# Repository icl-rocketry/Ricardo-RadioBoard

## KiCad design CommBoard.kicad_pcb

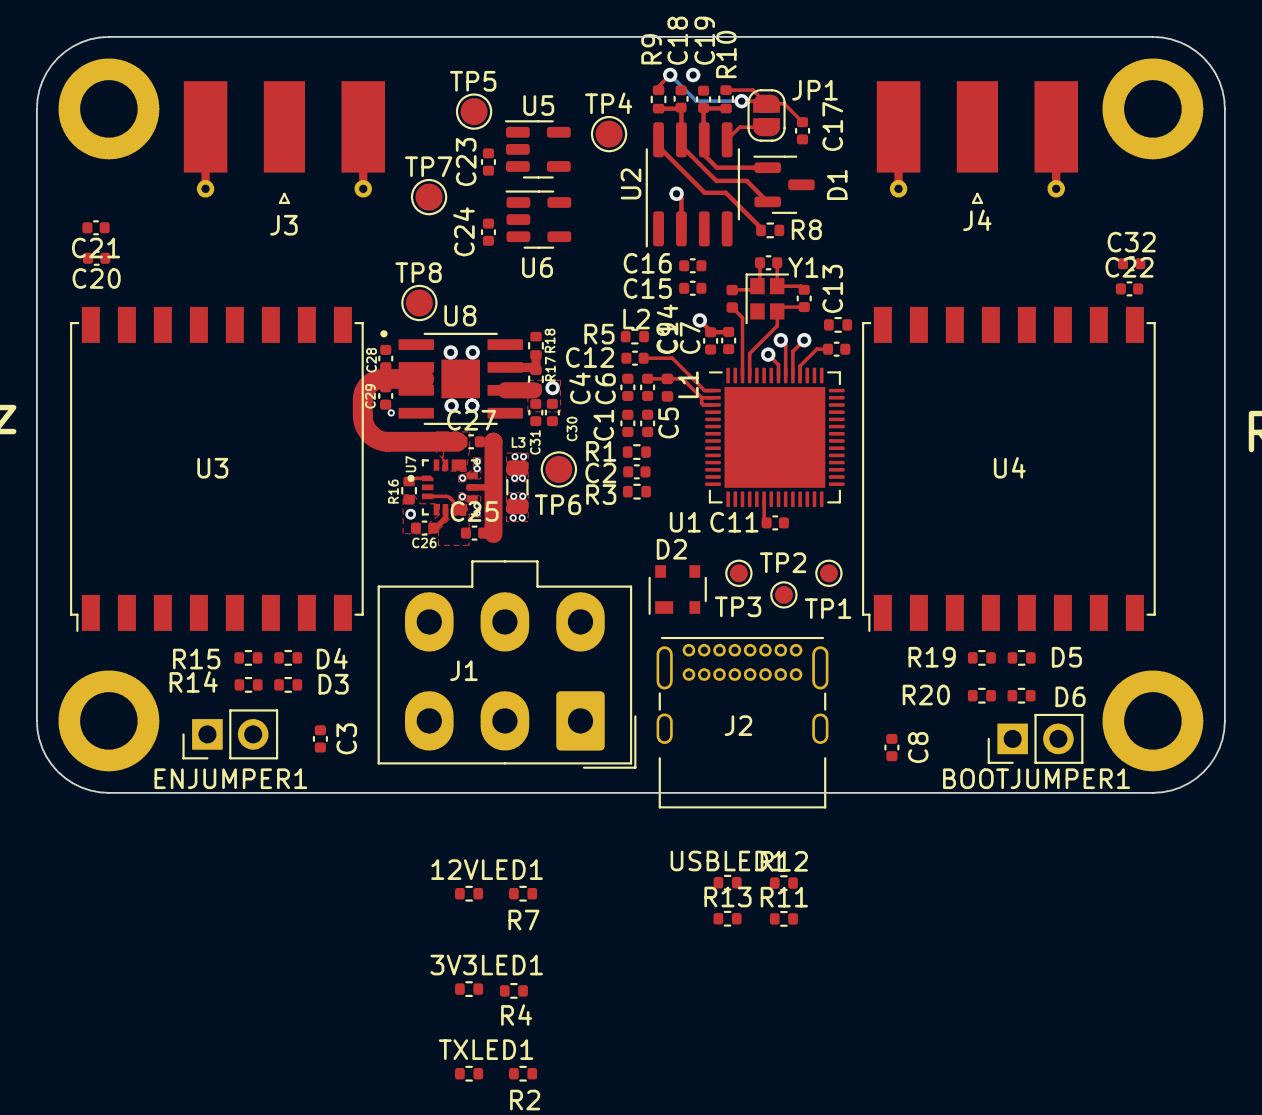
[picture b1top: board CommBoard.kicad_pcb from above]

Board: 4 copper layers, 66.0 x 42.0 mm, 93 parts (0 on the bottom side), 56 nets.

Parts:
3V3LED1: 3V3LED; R_0402_1005Metric
12VLED1: 12V_LED; R_0402_1005Metric
BOOTJUMPER1: Conn_01x02_Male; PinHeader_1x02_P2.54mm_Vertical
C1, C16, C20, C22, C25, C28, C30: 10uF; C_0402_1005Metric
C2, C4, C7, C26: 1uF; C_0402_1005Metric
C3, C5, C6, C8, C10, C11, C17, C21, C31, C32: 0.1uF; C_0402_1005Metric
C9: 10nF; C_0402_1005Metric
C12: 4.2pF; C_0402_1005Metric
C13, C14: C; C_0402_1005Metric
C15: 100nF; C_0402_1005Metric
C18, C19: 220pF; C_0402_1005Metric
C23, C24, C29: 4.7uF; C_0402_1005Metric
C27: 22uF; C_0402_1005Metric
D1: SM712_SOT23; SOT-23
D2: SP0503BAHT; SOT-143
D3, D4, D5, D6: LED_Small; R_0402_1005Metric
ENJUMPER1: Conn_01x02_Male; PinHeader_1x02_P2.54mm_Vertical
H1, H2, H3, H4: MountingHole_Pad; MountingHole_3.2mm_M3_DIN965_Pad
J1: RBUS; Molex_Mini-Fit_Jr_5566-06A_2x03_P4.20mm_Vertical
J2: USB_C_Receptacle_USB2.0; USB_C_Receptacle_GCT_USB4085
J3, J4: Conn_Coaxial; SMA_Molex_73251-1153_EdgeMount_Horizontal
JP1: TermJP; SolderJumper-2_P1.3mm_Open_RoundedPad1.0x1.5mm
L1: 2.0nH; L_0402_1005Metric
L2: 20nH; L_0402_1005Metric
L3: 1uH; L_0805_2012Metric
R1, R3: 10K; R_0402_1005Metric
R2, R4, R13, R14, R15, R19, R20: 470; R_0402_1005Metric
R5: 47.5; R_0402_1005Metric
R6: 499; R_0402_1005Metric
R7: 3k; R_0402_1005Metric
R8: 0; R_0402_1005Metric
R9, R10: 60; R_0402_1005Metric
R11, R12: 5.1k; R_0402_1005Metric
R16: 14k; R_0402_1005Metric
R17: 56k; R_0402_1005Metric
R18: 10k; R_0402_1005Metric
TP1, TP2, TP3: TestPoint; TestPoint_Pad_D1.0mm
TP4, TP5, TP6, TP7, TP8: TestPoint; TestPoint_Pad_D1.5mm
TXLED1: TX_LED; R_0402_1005Metric
U1: ESP32-S3; QFN-56-1EP_7x7mm_P0.4mm_EP5.6x5.6mm
U2: SN65HVD230; SOIC-8_3.9x4.9mm_P1.27mm
U3: RFM95W-868S2; HOPERF_RFM9XW_SMD
U4: RFM96W-433S2; HOPERF_RFM9XW_SMD
U5, U6: LM66100; SOT-23-5
U7: MAX77827AEFD+T; CONV_MAX77827AEFD+T
U8: SC4215; SOIC127P599X175-9N
USBLED1: USB_LED; R_0402_1005Metric
Y1: 40MHz±10ppm; Crystal_SMD_2016-4Pin_2.0x1.6mm

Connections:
+3V3: C1.1, C4.1, C5.1, C7.1, C9.1, C10.1, C11.1, C15.1, C16.1, C20.1, C21.1, C22.1, C30.2, C31.2, C32.1, L1.1, R1.1, R2.1, R3.1, R4.2, R17.1, TP6.1, U1.20 (VDD3P3_RTC), U1.46 (VDD3P3_CPU), U1.55 (VDDA), U1.56 (VDDA), U2.3 (VCC), U3.13 (3.3V), U4.13 (3.3V), U8.6 (VOUT)
+12V: J1.4, R7.1
/BOOT: BOOTJUMPER1.1, C8.1, R3.2, U1.5 (GPIO0/BOOT)
/CAN+: C18.2, D1.2 (A2), J1.5, R9.1, U2.7 (CANH)
/CAN-: C19.2, D1.1 (A1), J1.6, R10.2, U2.6 (CANL)
/CAN-BUS/Vref: JP1.1 (A), U2.5 (Vref)
/CAN_RX: U1.48 (MTMS/JTAG/GPIO42), U2.4 (R)
/CAN_TX: U1.47 (MTDI/JTAG/GPIO41), U2.1 (D)
/CHIP_PU: C2.1, C3.1, ENJUMPER1.1, R1.2, U1.4 (CHIP_PU/RESET)
/Data+: D2.4 (K), J2.A6 (D+), J2.B6 (D+), TP2.1, U1.26 (GPIO20/USB_D+/ADC2_CH9)
/Data-: D2.3 (K), J2.A7 (D-), J2.B7 (D-), TP1.1, U1.25 (GPIO19/USB_D-/ADC2_CH8)
/MISO: U1.37 (SPICLK_P/GPIO47), U3.3 (MOSI), U4.2 (MISO)
/MOSI: U1.36 (SPICLK_N/GPIO48), U3.2 (MISO), U4.3 (MOSI)
/Power/BBIN: C23.1, C24.1, C25.1, TP4.1, U5.5 (OUT), U6.5 (OUT), U7.3 (EN), U7.6 (IN)
/Power/BBOUT: C27.1, C28.1, C29.1, TP8.1, U7.11 (OUT), U7.13 (OUTS), U8.2 (EN), U8.3 (VIN)
/Power/BIAS: C26.1, U7.5 (BIAS)
/Power/FBIn: R17.2, R18.1, U8.7 (ADJ)
/Power/LX1: L3.1, U7.8 (LX1)
/Power/LX2: L3.2, U7.10 (LX2)
/Power/SEL: R16.1, U7.1 (SEL)
/R95_DIO0: U1.41 (GPIO36), U3.14 (DIO0)
/R95_NSS: U1.39 (GPIO34), U3.5 (NSS)
/R95_RESET: U1.40 (GPIO35), U3.6 (RESET)
/R95_RX: R15.2, U1.10 (GPIO5/ADC1_CH4)
/R95_TX: R14.2, U1.9 (GPIO4/ADC1_CH3)
/R96_DIO0: U1.27 (GPIO21), U4.14 (DIO0)
/R96_NSS: U1.42 (GPIO37), U4.5 (NSS)
/R96_RESET: U1.43 (GPIO38), U4.6 (RESET)
/R96_RX: R20.2, U1.12 (GPIO7/ADC1_CH6)
/R96_TX: R19.2, U1.11 (GPIO6/ADC1_CH5)
/SCK: U1.38 (GPIO33), U3.4 (SCK), U4.4 (SCK)
/TXD: R6.1, TXLED1.1 (K)
GND: 3V3LED1.1 (K), 12VLED1.1 (K), BOOTJUMPER1.2, C1.2, C2.2, C3.2, C4.2, C5.2, C6.2, C7.2, C8.2, C9.2, C10.2, C11.2, C13.2, C14.2, C15.2, C16.2, C17.2, C18.1, C19.1, C20.2, C21.2, C22.2, C23.2, C24.2, C25.2, C26.2, C27.2, C28.2, C29.2, C30.1, C31.1, C32.2, D1.3 (common), D2.1 (A), D3.1 (K), D4.1 (K), D5.1 (K), D6.1 (K), ENJUMPER1.2, H1.1, H2.1, H3.1, H4.1, J1.1, J1.2, J2.A1 (GND), J2.A12 (GND), J2.B1 (GND), J2.B12 (GND), J2.S1 (SHIELD), J3.2 (Ext), J4.2 (Ext), R5.1, R8.2, R11.2, R12.1, R16.2, R18.2, U1.57 (GND), U2.2 (GND), U3.1 (GND), U3.8 (GND), U3.10 (GND), U4.1 (GND), U4.8 (GND), U4.10 (GND), U5.2 (GND), U5.3 (CTL), U6.2 (GND), U6.3 (CTL), U7.4 (AGND), U7.9 (PGND), U8.8 (GND), U8.9 (GND), USBLED1.1 (K), Y1.2, Y1.4
unnamed: 3V3LED1.2 (A), R4.1
unnamed: 12VLED1.2 (A), R7.2
unnamed: C6.1, L1.2, U1.2 (VDD3P3), U1.3 (VDD3P3)
unnamed: C12.1, R5.2
unnamed: C12.2, U1.1 (LNA_IN/RF)
unnamed: C13.1, U1.53 (XTAL_N), Y1.3
unnamed: C14.1, L2.2, Y1.1
unnamed: C17.1, JP1.2 (B), R9.2, R10.1
unnamed: D3.2 (A), R14.1
unnamed: D4.2 (A), R15.1
unnamed: D5.2 (A), R19.1
unnamed: D6.2 (A), R20.1
unnamed: J2.A5 (CC1), R11.1
unnamed: J2.B5 (CC2), R12.2
unnamed: J3.1 (In), U3.9 (ANT)
unnamed: J4.1 (In), U4.9 (ANT)
unnamed: L2.1, U1.54 (XTAL_P)
unnamed: R2.2, TXLED1.2 (A)
unnamed: R6.2, U1.49 (U0TXD/PROG/GPIO43)
unnamed: R8.1, U2.8 (Rs)
unnamed: R13.2, USBLED1.2 (A)
RBUS_uC_V: J1.3, TP5.1, U5.1 (IN)
VBUS: D2.2 (K), J2.A4 (VBUS), J2.A9 (VBUS), J2.B4 (VBUS), J2.B9 (VBUS), R13.1, TP3.1, TP7.1, U6.1 (IN)

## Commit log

2022-11-19 Changed the Readme
2022-11-19 PCB Component Grouping
2022-11-26 New Template Update
2022-12-03 New Routing
2022-12-04 Grouping 2
2023-01-11 Most compressed board you'll see
